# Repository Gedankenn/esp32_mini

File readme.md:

# ESP32-C3 Mini Board – Hardware Design Documentation

**Author:** Fabio Slika Stella
**Target MCU:** ESP32-C3-MINI-1-N4
**Purpose:** Compact ESP32-C3 development board with USB-C power, onboard 3.3 V regulation, boot/reset buttons, status LED, and breakout header.

---

## Repository contents

| File | Content |
|------|---------|
| `esp32-mini.kicad_pro` | KiCad project (open this file) |
| `esp32-mini.kicad_sch` | Schematic (saved with KiCad 10) |
| `esp32-mini.kicad_pcb` | PCB layout (saved with KiCad 9 format) |
| `esp32-mini.kicad_prl` | KiCad local project settings |

The schematic was saved by KiCad 10, so it needs KiCad 10 or newer to open. Symbols come from the KiCad PCM SparkFun libraries plus project-specific `ESP32-C3-MINI-1-N4` and `AMS1117-3.3` symbols. No Gerbers, BOM export or firmware are included in the repository.

---

## 1. Overview

This board is designed as a minimal, robust ESP32-C3 platform focused on:

* USB-C powered operation
* Simple, well-known LDO regulation (AMS1117-3.3)
* Correct USB-C device identification
* Stable power integrity for Wi‑Fi operation
* Clean reset/boot circuitry
* Easy access to GPIOs through a 1×11 header

The schematic is divided into the following functional blocks:

1. USB-C power input
2. 3.3 V linear regulation
3. ESP32-C3 core circuit
4. Boot and reset buttons
5. Status LED
6. GPIO breakout connector

---

## 2. USB-C Power Input

### 2.1 USB-C Receptacle (J3)

The USB-C connector is used only as a **5 V power source** and optionally for **USB data (D+/D−)**.

Key design points:

* **VBUS → 5 V net** supplies the regulator input.
* **GND and shield** are tied to board ground for EMC and ESD robustness.
* **D+ and D−** are routed directly to the ESP32-C3 USB pins, enabling native USB functionality (CDC/JTAG/DFU).

### 2.2 CC Configuration Resistors (R1, R2 – 5.1 kΩ)

Two 5.1 kΩ pull-down resistors are connected from **CC1 and CC2 to GND**.

This advertises the board as a **USB device (UFP)** and ensures that any USB-C charger or host enables VBUS. Without these resistors, many USB-C power sources would not provide 5 V.

This follows the USB-C specification for default current mode.

### 2.3 Input Decoupling Capacitor

A **10 µF bulk capacitor** is placed near VBUS to:

* Absorb hot‑plug inrush current
* Reduce cable-induced transients
* Provide local energy storage before the LDO

---

## 3. 3.3 V Regulation Stage

### 3.1 Regulator Choice – AMS1117-3.3 (U6)

The AMS1117-3.3 is a classic linear regulator chosen for:

* High availability and low cost
* Simple application circuit
* Ability to supply the peak current required by ESP32-C3 (~400 mA bursts)

Although not the most efficient, it is electrically forgiving and ideal for USB-powered boards.

### 3.2 Input and Output Capacitors (C5, C6, C1, C2)

* **Input:** 10 µF + 0.1 µF
* **Output:** 10 µF + 0.1 µF

Reasons for this combination:

* 10 µF provides bulk energy storage and stabilizes the LDO control loop.
* 0.1 µF ceramic handles high-frequency noise and fast current spikes.

This is critical for ESP32 devices, which draw fast, high di/dt current during RF transmissions.

### 3.3 Power LED (R3 + D1)

A green LED connected to 3.3 V through a 180 Ω resistor provides:

* Visual confirmation that the regulator is active
* Quick debugging aid for power faults

The resistor value balances brightness and current consumption.

---

## 4. ESP32-C3 Core Circuit

### 4.1 Module Choice – ESP32-C3-MINI-1-N4

This module integrates:

* ESP32-C3 RISC‑V MCU
* 4 MB flash
* RF matching network and antenna

Using the module instead of the bare chip:

* Simplifies RF design
* Reduces certification risk
* Minimizes layout complexity

### 4.2 Power Decoupling (C7, C8)

Placed close to the 3V3 pin:

* 10 µF for bulk decoupling
* 0.1 µF for high-frequency suppression

This ensures local current delivery and reduces ground bounce and digital noise.

### 4.3 Enable (EN) Circuit (R6 + C15)

* **R6 (10 kΩ)** pulls EN up to 3.3 V.
* **C15 (10 µF)** to GND forms a power‑on reset delay.

Purpose:

* Guarantees a clean rising edge on EN
* Prevents unstable startup
* Ensures the ESP32 only boots after 3.3 V is fully settled

This RC network increases reliability during slow USB ramps or noisy power conditions.

---

## 5. Boot and Reset Buttons

Two buttons are provided to control ESP32 startup modes.

### 5.1 Reset / Enable Button (SW2 – chip_pu)

This button pulls **EN (chip_pu)** low when pressed, forcing a hardware reset.

Supporting components:

* 10 kΩ pull‑up keeps EN high during normal operation.
* 0.1 µF capacitor filters contact bounce and short spikes.

### 5.2 Boot Button (SW1 – GPIO9)

GPIO9 is a strapping pin used by ESP32-C3 to enter download/bootloader mode.

Pressing this button while resetting the chip forces USB boot mode, enabling firmware flashing.

Again, the RC network improves noise immunity and button behavior.

---

## 6. USB Data Connection

D+ and D− from the USB-C connector are routed directly to the ESP32-C3 USB pins.

This allows:

* Native USB CDC (serial)
* USB-JTAG debugging
* DFU-style firmware loading

No external USB‑UART is required, reducing cost and component count.

---

## 7. GPIO Breakout Connector

### 7.1 1×11 Header (J1)

This header exposes:

* Multiple GPIOs
* RXD0 / TXD0
* Power and ground references

Design goals:

* Breadboard-friendly development
* External sensor and peripheral connection
* Programming and debugging access

The selection prioritizes commonly used pins while avoiding conflict with USB and boot strapping pins.

---

## 8. Power Integrity and EMC Considerations

Several design choices were made specifically for ESP32 stability:

* Multiple local decoupling capacitors
* RC delay on EN
* Short power paths from regulator to MCU
* Ground-referenced USB shield

These minimize:

* Brownouts during Wi‑Fi transmission
* Spurious resets
* USB disconnections
* EMI-related malfunctions

---

## 9. Design Philosophy Summary

This board follows a **"minimal but electrically solid"** philosophy:

* Proven components instead of experimental ones
* Conservative decoupling strategy
* USB-C implemented according to spec
* Explicit support for flashing and recovery

The result is a compact ESP32-C3 platform suitable for:

* Embedded product prototypes
* Firmware development
* USB-based tools
* IoT experiments and low-volume hardware projects

---

## 10. Revision History

### v0.1.1 (2026-07-19)

**Fixes applied:**
- **AMS1117 tab (pad 4):** Changed from GND to 3V3 (VOUT). The SOT‑223 tab is VOUT in the fixed 3.3V AMS1117.
- **C15 EN capacitor:** Changed from 1 µF 0402 to 10 µF 0603. With R6=10 kΩ this gives ~100 ms RC delay.
- **C5 voltage rating:** 6.3 V → 10 V on the 5 V rail for proper safety margin. Only the PCB footprint was updated (`Voltage` = 10V). The schematic symbol is still `PCM_SparkFun-Capacitor:10uF_0603_6.3V_20%` with `Voltage` = 6.3V, so update the schematic (and BOM) before ordering.
- **Standardized net names:** `Io0` → `IO0`, `gpio9` → `IO9`, `I01..I04` → `IO1..IO4`
- **Silkscreen** updated to match new net names.

### Recommended Next Steps (do in KiCad GUI)

1. **Add debounce capacitor C16 (0.1 µF, 0402)** from IO9 (BOOT) to GND near SW1. Route tracks on PCB.
2. **Add ESD protection** on USB D+/D−. Use USBLC6‑2 (SOT‑23‑6) or SRV05‑4 between D+/D− and GND near J3.
3. **Add USB series termination** R7, R8 = 22 Ω (0603) on D+ and D− between J3 and U1. Mark as DNP — populate only if USB signal integrity issues arise.
4. **Add 4× M3 mounting holes** (3.2 mm) at board corners: (69, 56), (99.5, 56), (69, 84.5), (99.5, 84.5).
5. **AMS1117 stability:** Output capacitors are ceramic (very low ESR). AMS1117 requires ESR ≥ 0.1 Ω. Replace C1 with a 10 µF tantalum, or add a 1 Ω resistor in series with C1.
6. **Run DRC** after all changes.

---

## 11. Possible Future Improvements

* Replace AMS1117 with a high‑efficiency buck or low‑IQ LDO
* Add ESD diodes on USB D+/D−
* Add current measurement shunt
* Expose additional GPIOs
* Add battery support and charger IC

---

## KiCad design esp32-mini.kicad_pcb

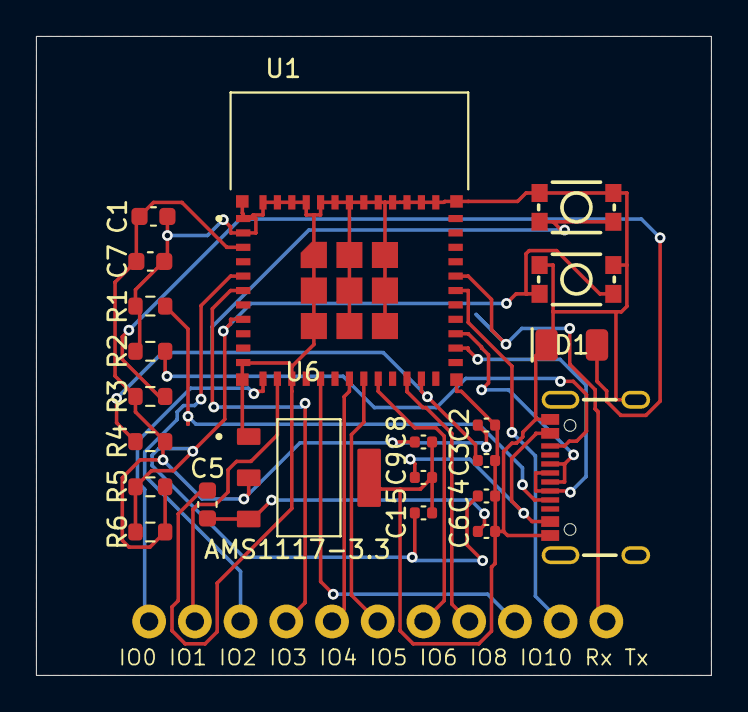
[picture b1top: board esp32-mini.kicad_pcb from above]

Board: 2 copper layers, 37.5 x 35.5 mm, 23 parts (0 on the bottom side), 22 nets.

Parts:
C1, C5, C7: 10uF; C_0603_1608Metric
C2, C3, C4, C6, C8, C9: 0.1uF; C_0402_1005Metric
C15: 10uF; C_0402_1005Metric
D1: Green; LED_1206_3216Metric_Green
J1: Conn_01x11; 1x11_P2.54mm
J3: USB_C_Receptacle; USB-C_16
R1, R2: 5.1k; R_0603_1608Metric
R3: 180; R_0603_1608Metric
R4, R5, R6: 10k; R_0603_1608Metric
SW1, SW2: SMD_4.6x2.8mm_h2.5mm; Push_SMD_4.6x2.8mm_h2.5mm
U1: ESP32-C3-MINI-1-N4; XCVR_ESP32-C3-MINI-1-N4
U6: AMS1117-3.3; SOT229P700X180-4N

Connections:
3V3: C1.1, C2.1, C7.1, C8.1, R3.1, R4.2, R5.2, R6.2, U1.3 (3V3), U6.2 (VOUT), U6.4 (VOUT)
5V: C5.1, C6.1, U6.3 (VIN)
D+: J3.A6 (D+), J3.B6 (D+), U1.27 (IO19)
D-: J3.A7 (D-), J3.B7 (D-), U1.26 (IO18)
GND: C1.2, C2.2, C3.2, C4.2, C5.2, C6.2, C7.2, C8.2, C9.2, C15.2, D1.1 (K), J3.GND, J3.S (SHIELD), R1.1, R2.1, SW1.1, SW2.1, U1.1 (GND), U1.2 (GND), U1.11 (GND), U1.14 (GND), U1.36 (GND), U1.37 (GND), U1.38 (GND), U1.39 (GND), U1.40 (GND), U1.41 (GND), U1.42 (GND), U1.43 (GND), U1.44 (GND), U1.45 (GND), U1.46 (GND), U1.47 (GND), U1.48 (GND), U1.49_1 (GND), U1.49_2 (GND), U1.49_3 (GND), U1.49_4 (GND), U1.49_5 (GND), U1.49_6 (GND), U1.49_7 (GND), U1.49_8 (GND), U1.49_9 (GND), U1.50 (GND), U1.51 (GND), U1.52 (GND), U1.53 (GND), U6.1 (GND)
IO0: J1.1, U1.12 (IO0)
IO1: J1.2, U1.13 (IO1)
IO2: J1.3, U1.5 (IO2)
IO3: J1.4, U1.6 (IO3)
IO4: J1.5, U1.18 (IO4)
IO5: J1.6, U1.19 (IO5)
IO6: J1.7, U1.20 (IO6)
IO8: J1.8, U1.22 (IO8)
IO9: C3.1, R4.1, SW1.2, U1.23 (IO9)
IO10: J1.9, U1.16 (IO10)
unnamed: D1.2 (A), R3.2
unnamed: J3.A5 (CC1), R1.2
unnamed: J3.B5 (CC2), R2.2
RxD0: J1.10, U1.30 (RXD0)
TxD0: J1.11, U1.31 (TXD0)
Vusb: C9.1, J3.VBUS
chip_pu: C4.1, C15.1, R5.1, R6.1, SW2.2, U1.8 (EN)

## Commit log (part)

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2026-01-13 update schematic and pcb layout
